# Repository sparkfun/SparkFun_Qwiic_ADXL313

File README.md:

SparkFun 3-Axis Digital Accelerometer Breakout - ADXL313 (Qwiic)
========================================

[*SparkFun 3-Axis Digital Accelerometer Breakout - ADXL313 (Qwiic) (WRL-15663)*](https://www.sparkfun.com/products/17241)

The ADXL313 is a low power, high resolution (up to 13-bits) 3-axis accelerometer for measurement up to ±4g. It measures the static acceleration of gravity in tilt-sensing applications, as well as dynamic acceleration resulting from motion or shock. Digital output data is formatted as 16-bit twos complement and is accessible through the on board Qwiic connectors (I<sup>2</sup>C) or SPI. Its high resolution and low noise enable resolution of inclination changes of as little as 0.1°, while a built-in FIFO facilitates using oversampling techniques to improve resolution to as little as 0.025° of inclination. The integrated 32-level FIFO can also be used to store data to minimize host processor intervention, resulting in reduced system power consumption. Additional low power modes enable intelligent motion-based power management with threshold sensing and active acceleration measurement at extremely low power dissipation. 

Getting the ADXL313 Qwiic breakout set-up is easy. Simply supply the accelerometer with power and communication via the Qwiic connector to your chosen Qwiic development board and you will be good to go. Example use cases for the ADXL313 from Analog Devices include car alarm, hill start aid (HSA) systems, electronic parking brakes, and data recorders applications  (black boxes).

Repository Contents
-------------------

* **/Hardware** - Eagle design files (.brd, .sch)
* **/Hardware/Production** - Production panel files (.brd)

Documentation
--------------
* **[Hookup Guide](https://learn.sparkfun.com/tutorials/sparkfun-qwiic-3-axis-accelerometer-adxl313-hookup-guide)** - Hookup guide for the SparkFun Qwiic 3-Axis Accelerometer (ADXL313)
* **[Product Repository](https://github.com/sparkfun/SparkFun_Qwiic_ADXL313)** - Main hardware repository (including schematic and board design files)

Product Versions
----------------
* [SEN-17241](https://www.sparkfun.com/products/17241)- v1.0, Initial Release

License Information
-------------------

This product is _**open source**_! 

Please review the LICENSE.md file for license information. 

If you have any questions or concerns on licensing, please contact technical support on our [SparkFun forums](https://forum.sparkfun.com/viewforum.php?f=152).

Distributed as-is; no warranty is given.

- Your friends at SparkFun.

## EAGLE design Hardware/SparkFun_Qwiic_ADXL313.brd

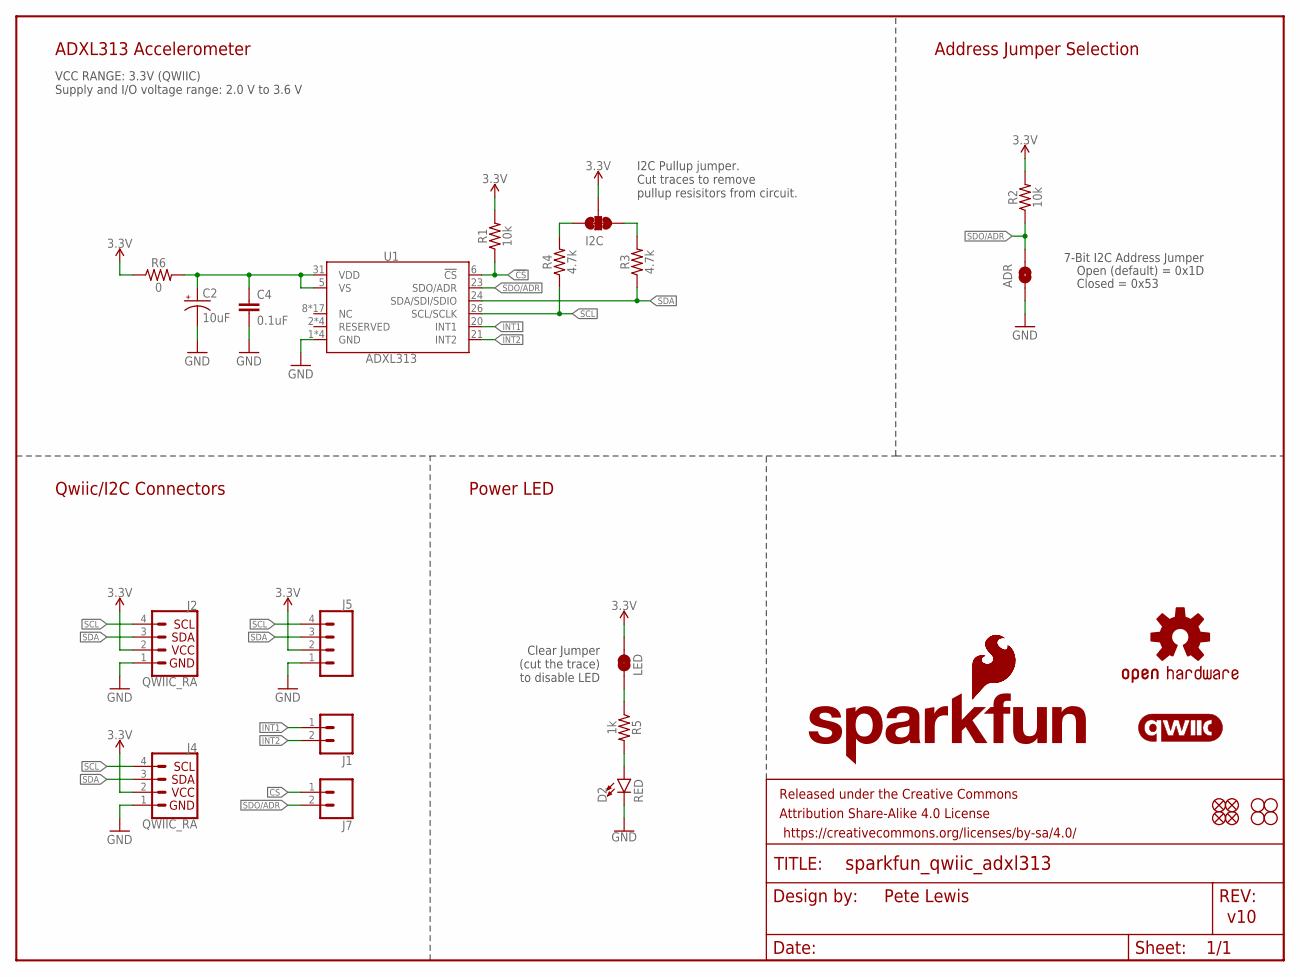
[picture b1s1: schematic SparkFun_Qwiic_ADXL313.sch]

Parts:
ADR: JUMPER-SMT_2_NO_SILK; SMT-JUMPER_2_NO_SILK
C2: 10uF; EIA3216
C4: 0.1uF; 0603
D2: RED; LED-0603
FRAME1: FRAME-LETTER; CREATIVE_COMMONS
I2C: JUMPER-SMT_3_2-NC_TRACE_SILK; SMT-JUMPER_3_2-NC_TRACE_SILK
J1, J7: CONN_021X02_NO_SILK; 1X02_NO_SILK
J2, J4: QWIIC_RA; JST04_1MM_RA
J5: CONN_041X04_NO_SILK; 1X04_NO_SILK
JP1: LED; SMT-JUMPER_2_NC_TRACE_SILK
JP2, JP5, JP6, JP11: FIDUCIALUFIDUCIAL; MICRO-FIDUCIAL
JP3, JP4, JP8, JP9: STAND-OFF
LOGO1: OSHW-LOGOMINI; OSHW-LOGO-MINI
LOGO2: SFE_LOGO_NAME_FLAME.1_INCH; SFE_LOGO_NAME_FLAME_.1
LOGO3: SFE_LOGO_FLAME.1_INCH; SFE_LOGO_FLAME_.1
LOGO4: QWIIC_LOGO_5MM; QWIIC_5MM
R1, R2: 10k; 0603
R3, R4: 4.7k; 0603
R5: 1k; 0603
R6: 0; 0603
U1: ADXL313; LFCSP

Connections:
3.3V: I2C.2, J2.2, J4.2, J5.2, JP1.2, R1.2, R2.2, R6.1
!CS: J7.1, R1.1, U1.6 (!CS)
GND: ADR.1, C2.C (-), C4.2, D2.C, J2.1, J4.1, J5.1, U1.1 (GND), U1.3 (GND), U1.4 (GND), U1.EPAD (GND)
INT1: J1.1, U1.20 (INT1)
INT2: J1.2, U1.21 (INT2)
unnamed: I2C.1, R3.2
unnamed: I2C.3, R4.2
unnamed: C2.A (+), C4.1, R6.2, U1.5 (VS), U1.31 (VDD)
unnamed: D2.A, R5.2
unnamed: JP1.1, R5.1
SCL: J2.4, J4.4, J5.4, R4.1, U1.26 (SCL/SCLK)
SDA: J2.3, J4.3, J5.3, R3.1, U1.24 (SDA/SDI/SDIO)
SDO/ADR: ADR.2, J7.2, R2.1, U1.23 (SDO/ADR)

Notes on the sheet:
7-Bit I2C Address Jumper
Closed = 0x53
Open (default) = 0x1D
Pete Lewis
v10
ADXL313 Accelerometer
Qwiic/I2C Connectors
I2C Pullup jumper. Cut traces to remove pullup resisitors from circuit.
Clear Jumper (cut the trace) to disable LED
Power LED
Address Jumper Selection
VCC RANGE: 3.3V (QWIIC) Supply and I/O voltage range: 2.0 V to 3.6 V

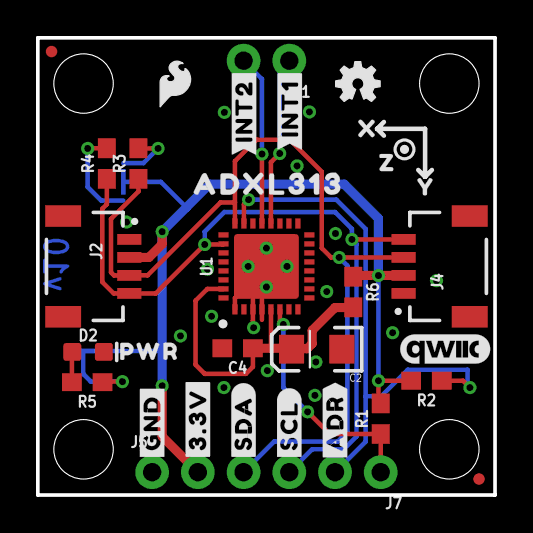
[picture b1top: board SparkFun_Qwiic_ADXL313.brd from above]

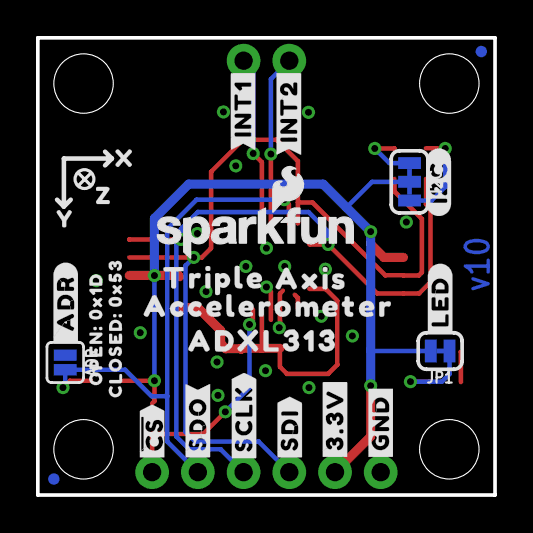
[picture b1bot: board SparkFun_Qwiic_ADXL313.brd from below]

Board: 2 copper layers, 25.4 x 25.4 mm, 63 parts (26 on the bottom side), 13 nets.

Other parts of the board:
U$1: TRIPLE0
U$2: AXIS0
U$3: ACCELEROMETER0
U$4, U$19: ADXL3130
U$5, U$6: #GND#0
U$7, U$8: #3#3V#0
U$9: #SDA#0
U$10: #SDI#0
U$11: #SCL#0
U$12: #_ADR#0
U$13, U$14: #INT2#0
U$15, U$16: #INT1#0
U$17, U$21: X0
U$18: ##CS##0
U$20: #SCLK#0
U$22: OPEN#_0X1D0
U$23: CLOSED#_0X530
U$24: #LED#0
U$25: PWR0
U$26, U$29: Y0
U$27: #I2C#0
U$28: #ADR#0
U$30: #SDO#0
U$31, U$32: Z0

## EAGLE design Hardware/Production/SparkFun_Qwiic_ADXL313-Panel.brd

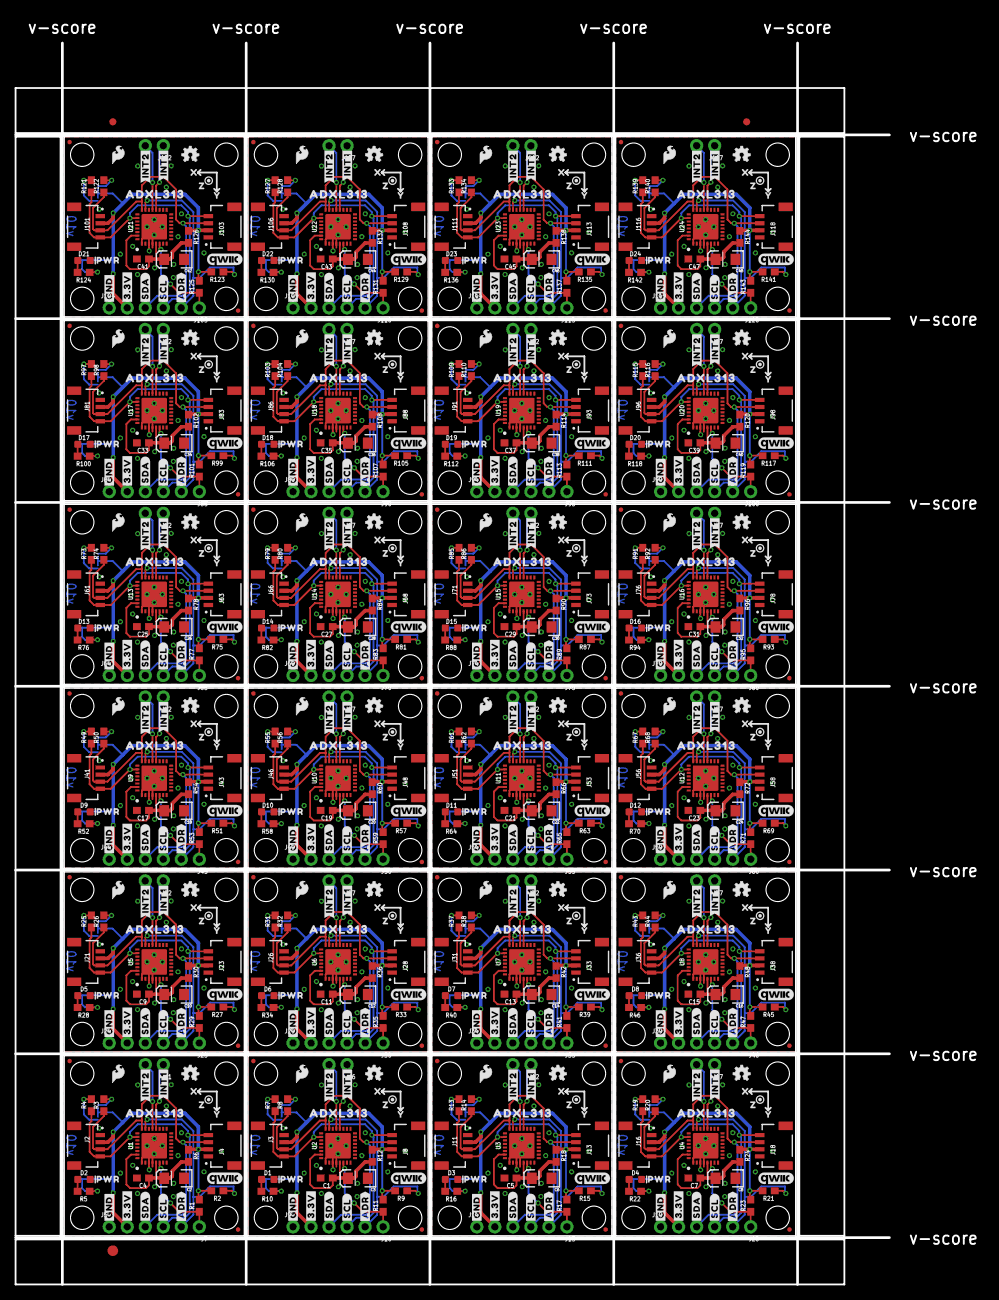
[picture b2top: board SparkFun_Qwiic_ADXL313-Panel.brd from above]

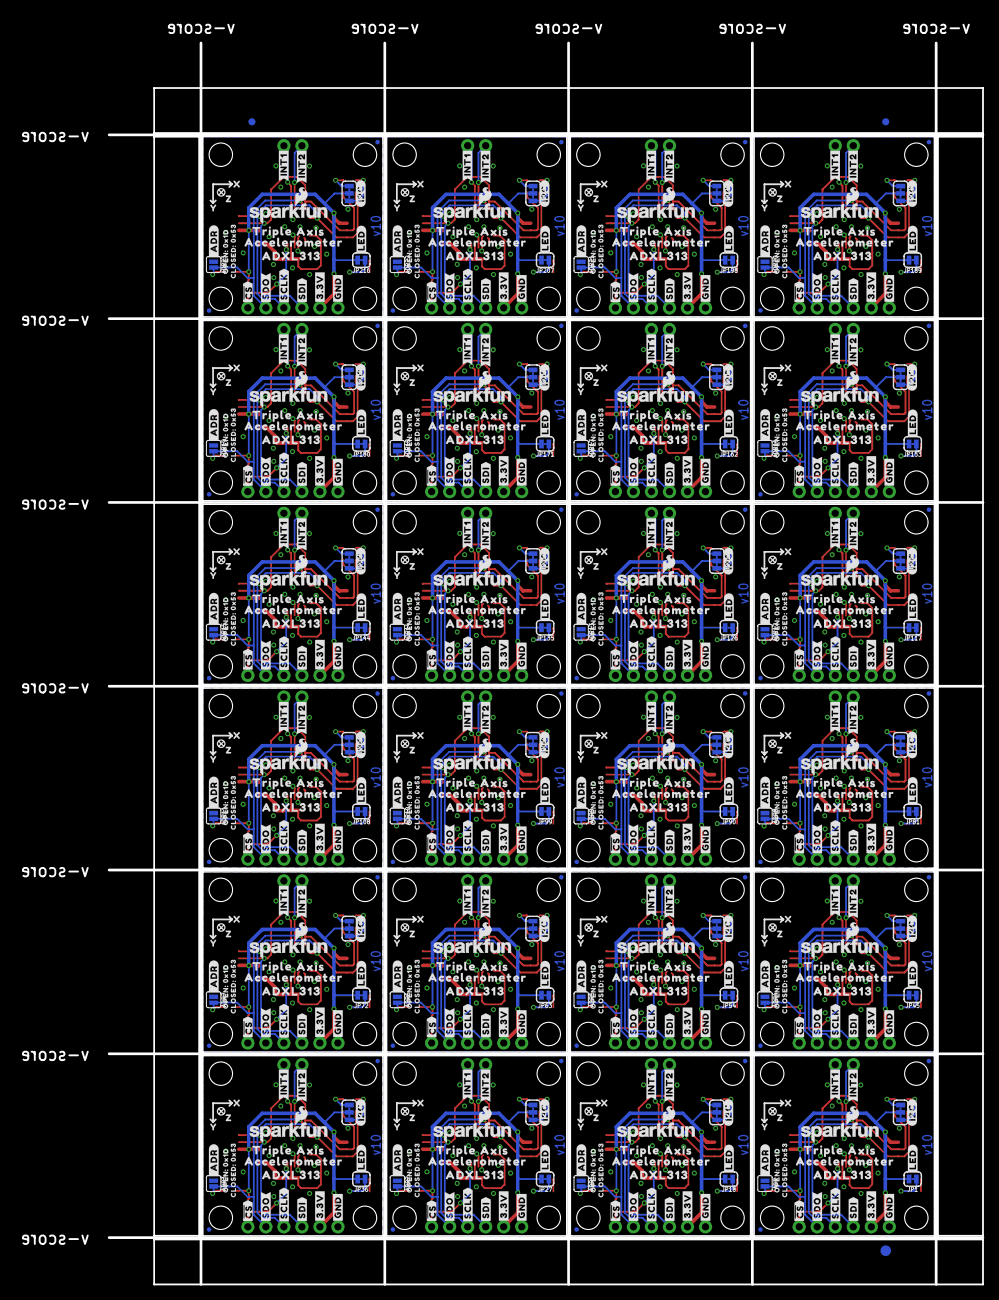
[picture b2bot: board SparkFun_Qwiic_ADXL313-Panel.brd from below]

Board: 2 copper layers, 136.4 x 178.9 mm, 1494 parts (627 on the bottom side), 312 nets.

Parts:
ADR, ADR1, ADR2, ADR3, ADR4, ADR5, ADR6, ADR7, ADR8, ADR9, ADR10, ADR11, ADR12, ADR13, ADR14, ADR15, ADR16, ADR17, ADR18, ADR19, ADR20, ADR21, ADR22, ADR23: SMT-JUMPER_2_NO_SILK
C1, C4, C5, C7, C9, C11, C13, C15, C17, C19, C21, C23, C25, C27, C29, C31, C33, C35, C37, C39, C41, C43, C45, C47: 0.1uF; 0603
C2, C3, C6, C8, C10, C12, C14, C16, C18, C20, C22, C24, C26, C28, C30, C32, C34, C36, C38, C40, C42, C44, C46, C48: 10uF; EIA3216
D1, D2, D3, D4, D5, D6, D7, D8, D9, D10, D11, D12, D13, D14, D15, D16, D17, D18, D19, D20, D21, D22, D23, D24: RED; LED-0603
E$1, E$2, E$3, E$4: FIDUCIAL-1X2
E$5, E$6: FIDUCIAL-1.5X3
I2C, I2C1, I2C2, I2C3, I2C4, I2C5, I2C6, I2C7, I2C8, I2C9, I2C10, I2C11, I2C12, I2C13, I2C14, I2C15, I2C16, I2C17, I2C18, I2C19, I2C20, I2C21, I2C22, I2C23: SMT-JUMPER_3_2-NC_TRACE_SILK
J1, J6, J7, J10, J12, J15, J17, J20, J22, J25, J27, J30, J32, J35, J37, J40, J42, J45, J47, J50, J52, J55, J57, J60, J62, J65, J67, J70, J72, J75, J77, J80, J82, J85, J87, J90, J92, J95, J97, J100, J102, J105, J107, J110, J112, J115, J117, J120: 1X02_NO_SILK
J2, J3, J4, J8, J11, J13, J16, J18, J21, J23, J26, J28, J31, J33, J36, J38, J41, J43, J46, J48, J51, J53, J56, J58, J61, J63, J66, J68, J71, J73, J76, J78, J81, J83, J86, J88, J91, J93, J96, J98, J101, J103, J106, J108, J111, J113, J116, J118: QWIIC_RA; JST04_1MM_RA
J5, J9, J14, J19, J24, J29, J34, J39, J44, J49, J54, J59, J64, J69, J74, J79, J84, J89, J94, J99, J104, J109, J114, J119: 1X04_NO_SILK
JP1, JP18, JP27, JP36, JP45, JP54, JP63, JP72, JP81, JP90, JP99, JP108, JP117, JP126, JP135, JP144, JP153, JP162, JP171, JP180, JP189, JP198, JP207, JP216: LED; SMT-JUMPER_2_NC_TRACE_SILK
JP2, JP5, JP6, JP11, JP12, JP13, JP14, JP15, JP21, JP22, JP23, JP24, JP30, JP31, JP32, JP33, JP39, JP40, JP41, JP42, JP48, JP49, JP50, JP51, JP57, JP58, JP59, JP60, JP66, JP67, JP68, JP69, JP75, JP76, JP77, JP78, JP84, JP85, JP86, JP87, JP93, JP94, JP95, JP96, JP102, JP103, JP104, JP105, JP111, JP112, JP113, JP114, JP120, JP121, JP122, JP123, JP129, JP130, JP131, JP132, JP138, JP139, JP140, JP141, JP147, JP148, JP149, JP150, JP156, JP157, JP158, JP159, JP165, JP166, JP167, JP168, JP174, JP175, JP176, JP177, JP183, JP184, JP185, JP186, JP192, JP193, JP194, JP195, JP201, JP202, JP203, JP204, JP210, JP211, JP212, JP213: FIDUCIALUFIDUCIAL; MICRO-FIDUCIAL
JP3, JP4, JP7, JP8, JP9, JP10, JP16, JP17, JP19, JP20, JP25, JP26, JP28, JP29, JP34, JP35, JP37, JP38, JP43, JP44, JP46, JP47, JP52, JP53, JP55, JP56, JP61, JP62, JP64, JP65, JP70, JP71, JP73, JP74, JP79, JP80, JP82, JP83, JP88, JP89, JP91, JP92, JP97, JP98, JP100, JP101, JP106, JP107, JP109, JP110, JP115, JP116, JP118, JP119, JP124, JP125, JP127, JP128, JP133, JP134, JP136, JP137, JP142, JP143, JP145, JP146, JP151, JP152, JP154, JP155, JP160, JP161, JP163, JP164, JP169, JP170, JP172, JP173, JP178, JP179, JP181, JP182, JP187, JP188, JP190, JP191, JP196, JP197, JP199, JP200, JP205, JP206, JP208, JP209, JP214, JP215: STAND-OFF
LOGO1, LOGO5, LOGO9, LOGO13, LOGO17, LOGO21, LOGO25, LOGO29, LOGO33, LOGO37, LOGO41, LOGO45, LOGO49, LOGO53, LOGO57, LOGO61, LOGO65, LOGO69, LOGO73, LOGO77, LOGO81, LOGO85, LOGO89, LOGO93: OSHW-LOGOMINI; OSHW-LOGO-MINI
LOGO2, LOGO6, LOGO10, LOGO14, LOGO18, LOGO22, LOGO26, LOGO30, LOGO34, LOGO38, LOGO42, LOGO46, LOGO50, LOGO54, LOGO58, LOGO62, LOGO66, LOGO70, LOGO74, LOGO78, LOGO82, LOGO86, LOGO90, LOGO94: SFE_LOGO_NAME_FLAME.1_INCH; SFE_LOGO_NAME_FLAME_.1
LOGO3, LOGO8, LOGO12, LOGO16, LOGO20, LOGO24, LOGO28, LOGO32, LOGO36, LOGO40, LOGO44, LOGO48, LOGO52, LOGO56, LOGO60, LOGO64, LOGO68, LOGO72, LOGO76, LOGO80, LOGO84, LOGO88, LOGO92, LOGO96: SFE_LOGO_FLAME.1_INCH; SFE_LOGO_FLAME_.1
LOGO4, LOGO7, LOGO11, LOGO15, LOGO19, LOGO23, LOGO27, LOGO31, LOGO35, LOGO39, LOGO43, LOGO47, LOGO51, LOGO55, LOGO59, LOGO63, LOGO67, LOGO71, LOGO75, LOGO79, LOGO83, LOGO87, LOGO91, LOGO95: QWIIC_LOGO_5MM; QWIIC_5MM
R1, R2, R9, R11, R15, R17, R21, R23, R27, R29, R33, R35, R39, R41, R45, R47, R51, R53, R57, R59, R63, R65, R69, R71, R75, R77, R81, R83, R87, R89, R93, R95, R99, R101, R105, R107, R111, R113, R117, R119, R123, R125, R129, R131, R135, R137, R141, R143: 10k; 0603
R3, R4, R7, R8, R13, R14, R19, R20, R25, R26, R31, R32, R37, R38, R43, R44, R49, R50, R55, R56, R61, R62, R67, R68, R73, R74, R79, R80, R85, R86, R91, R92, R97, R98, R103, R104, R109, R110, R115, R116, R121, R122, R127, R128, R133, R134, R139, R140: 4.7k; 0603
R5, R10, R16, R22, R28, R34, R40, R46, R52, R58, R64, R70, R76, R82, R88, R94, R100, R106, R112, R118, R124, R130, R136, R142: 1k; 0603
R6, R12, R18, R24, R30, R36, R42, R48, R54, R60, R66, R72, R78, R84, R90, R96, R102, R108, R114, R120, R126, R132, R138, R144: 0; 0603
U1, U2, U3, U4, U5, U6, U7, U8, U9, U10, U11, U12, U13, U14, U15, U16, U17, U18, U19, U20, U21, U22, U23, U24: ADXL313; LFCSP
U$1, U$33, U$65, U$97, U$129, U$161, U$193, U$225, U$257, U$289, U$321, U$353, U$385, U$417, U$449, U$481, U$513, U$545, U$577, U$609, U$641, U$673, U$705, U$737: TRIPLE0
U$2, U$34, U$66, U$98, U$130, U$162, U$194, U$226, U$258, U$290, U$322, U$354, U$386, U$418, U$450, U$482, U$514, U$546, U$578, U$610, U$642, U$674, U$706, U$738: AXIS0
U$3, U$35, U$67, U$99, U$131, U$163, U$195, U$227, U$259, U$291, U$323, U$355, U$387, U$419, U$451, U$483, U$515, U$547, U$579, U$611, U$643, U$675, U$707, U$739: ACCELEROMETER0
U$4, U$19, U$36, U$52, U$68, U$84, U$100, U$116, U$132, U$148, U$164, U$180, U$196, U$212, U$228, U$244, U$260, U$276, U$292, U$308, U$324, U$340, U$356, U$372, U$388, U$404, U$420, U$436, U$452, U$468, U$484, U$500, U$516, U$532, U$548, U$564, U$580, U$596, U$612, U$628, U$644, U$660, U$676, U$692, U$708, U$724, U$740, U$756: ADXL3130
U$5, U$6, U$37, U$38, U$69, U$70, U$101, U$102, U$133, U$134, U$165, U$166, U$197, U$198, U$229, U$230, U$261, U$262, U$293, U$294, U$325, U$326, U$357, U$358, U$389, U$390, U$421, U$422, U$453, U$454, U$485, U$486, U$517, U$518, U$549, U$550, U$581, U$582, U$613, U$614, U$645, U$646, U$677, U$678, U$709, U$710, U$741, U$742: #GND#0
U$7, U$8, U$39, U$40, U$71, U$72, U$103, U$104, U$135, U$136, U$167, U$168, U$199, U$200, U$231, U$232, U$263, U$264, U$295, U$296, U$327, U$328, U$359, U$360, U$391, U$392, U$423, U$424, U$455, U$456, U$487, U$488, U$519, U$520, U$551, U$552, U$583, U$584, U$615, U$616, U$647, U$648, U$679, U$680, U$711, U$712, U$743, U$744: #3#3V#0
U$9, U$41, U$73, U$105, U$137, U$169, U$201, U$233, U$265, U$297, U$329, U$361, U$393, U$425, U$457, U$489, U$521, U$553, U$585, U$617, U$649, U$681, U$713, U$745: #SDA#0
U$10, U$56, U$88, U$120, U$152, U$184, U$216, U$248, U$280, U$312, U$344, U$376, U$408, U$440, U$472, U$504, U$536, U$568, U$600, U$632, U$664, U$696, U$728, U$760: #SDI#0
U$11, U$42, U$74, U$106, U$138, U$170, U$202, U$234, U$266, U$298, U$330, U$362, U$394, U$426, U$458, U$490, U$522, U$554, U$586, U$618, U$650, U$682, U$714, U$746: #SCL#0
U$12, U$58, U$90, U$122, U$154, U$186, U$218, U$250, U$282, U$314, U$346, U$378, U$410, U$442, U$474, U$506, U$538, U$570, U$602, U$634, U$666, U$698, U$730, U$762: #_ADR#0
U$13, U$14, U$43, U$44, U$75, U$76, U$107, U$108, U$139, U$140, U$171, U$172, U$203, U$204, U$235, U$236, U$267, U$268, U$299, U$300, U$331, U$332, U$363, U$364, U$395, U$396, U$427, U$428, U$459, U$460, U$491, U$492, U$523, U$524, U$555, U$556, U$587, U$588, U$619, U$620, U$651, U$652, U$683, U$684, U$715, U$716, U$747, U$748: #INT2#0
U$15, U$16, U$45, U$46, U$77, U$78, U$109, U$110, U$141, U$142, U$173, U$174, U$205, U$206, U$237, U$238, U$269, U$270, U$301, U$302, U$333, U$334, U$365, U$366, U$397, U$398, U$429, U$430, U$461, U$462, U$493, U$494, U$525, U$526, U$557, U$558, U$589, U$590, U$621, U$622, U$653, U$654, U$685, U$686, U$717, U$718, U$749, U$750: #INT1#0
U$17, U$21, U$59, U$60, U$91, U$92, U$123, U$124, U$155, U$156, U$187, U$188, U$219, U$220, U$251, U$252, U$283, U$284, U$315, U$316, U$347, U$348, U$379, U$380, U$411, U$412, U$443, U$444, U$475, U$476, U$507, U$508, U$539, U$540, U$571, U$572, U$603, U$604, U$635, U$636, U$667, U$668, U$699, U$700, U$731, U$732, U$763, U$764: X0
U$18, U$47, U$79, U$111, U$143, U$175, U$207, U$239, U$271, U$303, U$335, U$367, U$399, U$431, U$463, U$495, U$527, U$559, U$591, U$623, U$655, U$687, U$719, U$751: ##CS##0
U$20, U$57, U$89, U$121, U$153, U$185, U$217, U$249, U$281, U$313, U$345, U$377, U$409, U$441, U$473, U$505, U$537, U$569, U$601, U$633, U$665, U$697, U$729, U$761: #SCLK#0
U$22, U$48, U$80, U$112, U$144, U$176, U$208, U$240, U$272, U$304, U$336, U$368, U$400, U$432, U$464, U$496, U$528, U$560, U$592, U$624, U$656, U$688, U$720, U$752: OPEN#_0X1D0
U$23, U$49, U$81, U$113, U$145, U$177, U$209, U$241, U$273, U$305, U$337, U$369, U$401, U$433, U$465, U$497, U$529, U$561, U$593, U$625, U$657, U$689, U$721, U$753: CLOSED#_0X530
U$24, U$50, U$82, U$114, U$146, U$178, U$210, U$242, U$274, U$306, U$338, U$370, U$402, U$434, U$466, U$498, U$530, U$562, U$594, U$626, U$658, U$690, U$722, U$754: #LED#0
U$25, U$51, U$83, U$115, U$147, U$179, U$211, U$243, U$275, U$307, U$339, U$371, U$403, U$435, U$467, U$499, U$531, U$563, U$595, U$627, U$659, U$691, U$723, U$755: PWR0
U$26, U$29, U$61, U$62, U$93, U$94, U$125, U$126, U$157, U$158, U$189, U$190, U$221, U$222, U$253, U$254, U$285, U$286, U$317, U$318, U$349, U$350, U$381, U$382, U$413, U$414, U$445, U$446, U$477, U$478, U$509, U$510, U$541, U$542, U$573, U$574, U$605, U$606, U$637, U$638, U$669, U$670, U$701, U$702, U$733, U$734, U$765, U$766: Y0
U$27, U$53, U$85, U$117, U$149, U$181, U$213, U$245, U$277, U$309, U$341, U$373, U$405, U$437, U$469, U$501, U$533, U$565, U$597, U$629, U$661, U$693, U$725, U$757: #I2C#0
U$28, U$55, U$87, U$119, U$151, U$183, U$215, U$247, U$279, U$311, U$343, U$375, U$407, U$439, U$471, U$503, U$535, U$567, U$599, U$631, U$663, U$695, U$727, U$759: #ADR#0
U$30, U$54, U$86, U$118, U$150, U$182, U$214, U$246, U$278, U$310, U$342, U$374, U$406, U$438, U$470, U$502, U$534, U$566, U$598, U$630, U$662, U$694, U$726, U$758: #SDO#0
U$31, U$32, U$63, U$64, U$95, U$96, U$127, U$128, U$159, U$160, U$191, U$192, U$223, U$224, U$255, U$256, U$287, U$288, U$319, U$320, U$351, U$352, U$383, U$384, U$415, U$416, U$447, U$448, U$479, U$480, U$511, U$512, U$543, U$544, U$575, U$576, U$607, U$608, U$639, U$640, U$671, U$672, U$703, U$704, U$735, U$736, U$767, U$768: Z0

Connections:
3.3V: I2C.2, J2.2, J4.2, J5.2, JP1.2, R1.2, R2.2, R6.1
3.3V1: I2C1.2, J3.2, J8.2, J9.2, JP18.2, R9.2, R11.2, R12.1
3.3V2: I2C2.2, J11.2, J13.2, J14.2, JP27.2, R15.2, R17.2, R18.1
3.3V3: I2C3.2, J16.2, J18.2, J19.2, JP36.2, R21.2, R23.2, R24.1
3.3V4: I2C4.2, J21.2, J23.2, J24.2, JP45.2, R27.2, R29.2, R30.1
3.3V5: I2C5.2, J26.2, J28.2, J29.2, JP54.2, R33.2, R35.2, R36.1
3.3V6: I2C6.2, J31.2, J33.2, J34.2, JP63.2, R39.2, R41.2, R42.1
3.3V7: I2C7.2, J36.2, J38.2, J39.2, JP72.2, R45.2, R47.2, R48.1
3.3V8: I2C8.2, J41.2, J43.2, J44.2, JP81.2, R51.2, R53.2, R54.1
3.3V9: I2C9.2, J46.2, J48.2, J49.2, JP90.2, R57.2, R59.2, R60.1
3.3V10: I2C10.2, J51.2, J53.2, J54.2, JP99.2, R63.2, R65.2, R66.1
3.3V11: I2C11.2, J56.2, J58.2, J59.2, JP108.2, R69.2, R71.2, R72.1
3.3V12: I2C12.2, J61.2, J63.2, J64.2, JP117.2, R75.2, R77.2, R78.1
3.3V13: I2C13.2, J66.2, J68.2, J69.2, JP126.2, R81.2, R83.2, R84.1
3.3V14: I2C14.2, J71.2, J73.2, J74.2, JP135.2, R87.2, R89.2, R90.1
3.3V15: I2C15.2, J76.2, J78.2, J79.2, JP144.2, R93.2, R95.2, R96.1
3.3V16: I2C16.2, J81.2, J83.2, J84.2, JP153.2, R99.2, R101.2, R102.1
3.3V17: I2C17.2, J86.2, J88.2, J89.2, JP162.2, R105.2, R107.2, R108.1
3.3V18: I2C18.2, J91.2, J93.2, J94.2, JP171.2, R111.2, R113.2, R114.1
3.3V19: I2C19.2, J96.2, J98.2, J99.2, JP180.2, R117.2, R119.2, R120.1
3.3V20: I2C20.2, J101.2, J103.2, J104.2, JP189.2, R123.2, R125.2, R126.1
3.3V21: I2C21.2, J106.2, J108.2, J109.2, JP198.2, R129.2, R131.2, R132.1
3.3V22: I2C22.2, J111.2, J113.2, J114.2, JP207.2, R135.2, R137.2, R138.1
3.3V23: I2C23.2, J116.2, J118.2, J119.2, JP216.2, R141.2, R143.2, R144.1
!CS: J7.1, R1.1, U1.6
!CS1: J10.1, R11.1, U2.6
!CS2: J15.1, R17.1, U3.6
!CS3: J20.1, R23.1, U4.6
!CS4: J25.1, R29.1, U5.6
!CS5: J30.1, R35.1, U6.6
!CS6: J35.1, R41.1, U7.6
!CS7: J40.1, R47.1, U8.6
!CS8: J45.1, R53.1, U9.6
!CS9: J50.1, R59.1, U10.6
!CS10: J55.1, R65.1, U11.6
!CS11: J60.1, R71.1, U12.6
!CS12: J65.1, R77.1, U13.6
!CS13: J70.1, R83.1, U14.6
!CS14: J75.1, R89.1, U15.6
!CS15: J80.1, R95.1, U16.6
!CS16: J85.1, R101.1, U17.6
!CS17: J90.1, R107.1, U18.6
!CS18: J95.1, R113.1, U19.6
!CS19: J100.1, R119.1, U20.6
!CS20: J105.1, R125.1, U21.6
!CS21: J110.1, R131.1, U22.6
!CS22: J115.1, R137.1, U23.6
!CS23: J120.1, R143.1, U24.6
GND: ADR.1, C2.C, C4.2, D2.C, J2.1, J4.1, J5.1, U1.1, U1.3, U1.4, U1.EPAD
GND1: ADR1.1, C1.2, C3.C, D1.C, J3.1, J8.1, J9.1, U2.1, U2.3, U2.4, U2.EPAD
GND2: ADR2.1, C5.2, C6.C, D3.C, J11.1, J13.1, J14.1, U3.1, U3.3, U3.4, U3.EPAD
GND3: ADR3.1, C7.2, C8.C, D4.C, J16.1, J18.1, J19.1, U4.1, U4.3, U4.4, U4.EPAD
GND4: ADR4.1, C9.2, C10.C, D5.C, J21.1, J23.1, J24.1, U5.1, U5.3, U5.4, U5.EPAD
GND5: ADR5.1, C11.2, C12.C, D6.C, J26.1, J28.1, J29.1, U6.1, U6.3, U6.4, U6.EPAD
GND6: ADR6.1, C13.2, C14.C, D7.C, J31.1, J33.1, J34.1, U7.1, U7.3, U7.4, U7.EPAD
GND7: ADR7.1, C15.2, C16.C, D8.C, J36.1, J38.1, J39.1, U8.1, U8.3, U8.4, U8.EPAD
GND8: ADR8.1, C17.2, C18.C, D9.C, J41.1, J43.1, J44.1, U9.1, U9.3, U9.4, U9.EPAD
GND9: ADR9.1, C19.2, C20.C, D10.C, J46.1, J48.1, J49.1, U10.1, U10.3, U10.4, U10.EPAD
GND10: ADR10.1, C21.2, C22.C, D11.C, J51.1, J53.1, J54.1, U11.1, U11.3, U11.4, U11.EPAD
GND11: ADR11.1, C23.2, C24.C, D12.C, J56.1, J58.1, J59.1, U12.1, U12.3, U12.4, U12.EPAD
GND12: ADR12.1, C25.2, C26.C, D13.C, J61.1, J63.1, J64.1, U13.1, U13.3, U13.4, U13.EPAD
GND13: ADR13.1, C27.2, C28.C, D14.C, J66.1, J68.1, J69.1, U14.1, U14.3, U14.4, U14.EPAD
GND14: ADR14.1, C29.2, C30.C, D15.C, J71.1, J73.1, J74.1, U15.1, U15.3, U15.4, U15.EPAD
GND15: ADR15.1, C31.2, C32.C, D16.C, J76.1, J78.1, J79.1, U16.1, U16.3, U16.4, U16.EPAD
GND16: ADR16.1, C33.2, C34.C, D17.C, J81.1, J83.1, J84.1, U17.1, U17.3, U17.4, U17.EPAD
GND17: ADR17.1, C35.2, C36.C, D18.C, J86.1, J88.1, J89.1, U18.1, U18.3, U18.4, U18.EPAD
GND18: ADR18.1, C37.2, C38.C, D19.C, J91.1, J93.1, J94.1, U19.1, U19.3, U19.4, U19.EPAD
GND19: ADR19.1, C39.2, C40.C, D20.C, J96.1, J98.1, J99.1, U20.1, U20.3, U20.4, U20.EPAD
GND20: ADR20.1, C41.2, C42.C, D21.C, J101.1, J103.1, J104.1, U21.1, U21.3, U21.4, U21.EPAD
GND21: ADR21.1, C43.2, C44.C, D22.C, J106.1, J108.1, J109.1, U22.1, U22.3, U22.4, U22.EPAD
GND22: ADR22.1, C45.2, C46.C, D23.C, J111.1, J113.1, J114.1, U23.1, U23.3, U23.4, U23.EPAD
GND23: ADR23.1, C47.2, C48.C, D24.C, J116.1, J118.1, J119.1, U24.1, U24.3, U24.4, U24.EPAD
INT1: J1.1, U1.20
INT2: J1.2, U1.21
INT3: J6.2, U2.21
INT4: J6.1, U2.20
INT5: J12.2, U3.21
INT6: J12.1, U3.20
INT7: J17.2, U4.21
INT8: J17.1, U4.20
INT9: J22.2, U5.21
INT10: J22.1, U5.20
INT11: J27.2, U6.21
INT12: J27.1, U6.20
INT13: J32.2, U7.21
INT14: J32.1, U7.20
INT15: J37.2, U8.21
INT16: J37.1, U8.20
INT17: J42.2, U9.21
INT18: J42.1, U9.20
INT19: J47.2, U10.21
INT20: J47.1, U10.20
INT21: J52.2, U11.21
INT22: J52.1, U11.20
INT23: J57.2, U12.21
INT24: J57.1, U12.20
INT25: J62.2, U13.21
INT26: J62.1, U13.20
INT27: J67.2, U14.21
INT28: J67.1, U14.20
INT29: J72.2, U15.21
INT30: J72.1, U15.20
INT31: J77.2, U16.21
INT32: J77.1, U16.20
INT33: J82.2, U17.21
INT34: J82.1, U17.20
INT35: J87.2, U18.21
INT36: J87.1, U18.20
INT37: J92.2, U19.21
INT38: J92.1, U19.20
INT39: J97.2, U20.21
INT40: J97.1, U20.20
INT41: J102.2, U21.21
INT42: J102.1, U21.20
INT43: J107.2, U22.21
INT44: J107.1, U22.20
INT45: J112.2, U23.21
INT46: J112.1, U23.20
INT47: J117.2, U24.21
INT48: J117.1, U24.20
unnamed: I2C.1, R3.2
unnamed: I2C.3, R4.2
unnamed: C2.A, C4.1, R6.2, U1.5, U1.31
unnamed: I2C1.1, R8.2
unnamed: I2C1.3, R7.2
unnamed: D2.A, R5.2
unnamed: D1.A, R10.2
unnamed: JP1.1, R5.1
unnamed: JP18.1, R10.1
unnamed: C1.1, C3.A, R12.2, U2.5, U2.31
unnamed: I2C2.1, R14.2
unnamed: I2C2.3, R13.2
unnamed: D3.A, R16.2
unnamed: JP27.1, R16.1
unnamed: C5.1, C6.A, R18.2, U3.5, U3.31
unnamed: I2C3.1, R20.2
unnamed: I2C3.3, R19.2
unnamed: D4.A, R22.2
unnamed: JP36.1, R22.1
unnamed: C7.1, C8.A, R24.2, U4.5, U4.31
unnamed: I2C4.1, R26.2
unnamed: I2C4.3, R25.2
unnamed: D5.A, R28.2
unnamed: JP45.1, R28.1
unnamed: C9.1, C10.A, R30.2, U5.5, U5.31
unnamed: I2C5.1, R32.2
unnamed: I2C5.3, R31.2
unnamed: D6.A, R34.2
unnamed: JP54.1, R34.1
unnamed: C11.1, C12.A, R36.2, U6.5, U6.31
unnamed: I2C6.1, R38.2
unnamed: I2C6.3, R37.2
unnamed: D7.A, R40.2
unnamed: JP63.1, R40.1
unnamed: C13.1, C14.A, R42.2, U7.5, U7.31
unnamed: I2C7.1, R44.2
unnamed: I2C7.3, R43.2
unnamed: D8.A, R46.2
unnamed: JP72.1, R46.1
unnamed: C15.1, C16.A, R48.2, U8.5, U8.31
unnamed: I2C8.1, R50.2
unnamed: I2C8.3, R49.2
unnamed: D9.A, R52.2
unnamed: JP81.1, R52.1
unnamed: C17.1, C18.A, R54.2, U9.5, U9.31
unnamed: I2C9.1, R56.2
unnamed: I2C9.3, R55.2
unnamed: D10.A, R58.2
unnamed: JP90.1, R58.1
unnamed: C19.1, C20.A, R60.2, U10.5, U10.31
unnamed: I2C10.1, R62.2
unnamed: I2C10.3, R61.2
unnamed: D11.A, R64.2
unnamed: JP99.1, R64.1
unnamed: C21.1, C22.A, R66.2, U11.5, U11.31
unnamed: I2C11.1, R68.2
unnamed: I2C11.3, R67.2
unnamed: D12.A, R70.2
unnamed: JP108.1, R70.1
unnamed: C23.1, C24.A, R72.2, U12.5, U12.31
unnamed: I2C12.1, R74.2
unnamed: I2C12.3, R73.2
unnamed: D13.A, R76.2
unnamed: JP117.1, R76.1
unnamed: C25.1, C26.A, R78.2, U13.5, U13.31
unnamed: I2C13.1, R80.2
unnamed: I2C13.3, R79.2
unnamed: D14.A, R82.2
unnamed: JP126.1, R82.1
unnamed: C27.1, C28.A, R84.2, U14.5, U14.31
unnamed: I2C14.1, R86.2
unnamed: I2C14.3, R85.2
unnamed: D15.A, R88.2
unnamed: JP135.1, R88.1
unnamed: C29.1, C30.A, R90.2, U15.5, U15.31
unnamed: I2C15.1, R92.2
unnamed: I2C15.3, R91.2
unnamed: D16.A, R94.2
unnamed: JP144.1, R94.1
unnamed: C31.1, C32.A, R96.2, U16.5, U16.31
unnamed: I2C16.1, R98.2
unnamed: I2C16.3, R97.2
unnamed: D17.A, R100.2
unnamed: JP153.1, R100.1
unnamed: C33.1, C34.A, R102.2, U17.5, U17.31
unnamed: I2C17.1, R104.2
unnamed: I2C17.3, R103.2
unnamed: D18.A, R106.2
unnamed: JP162.1, R106.1
unnamed: C35.1, C36.A, R108.2, U18.5, U18.31
unnamed: I2C18.1, R110.2
unnamed: I2C18.3, R109.2
unnamed: D19.A, R112.2
unnamed: JP171.1, R112.1
unnamed: C37.1, C38.A, R114.2, U19.5, U19.31
unnamed: I2C19.1, R116.2
unnamed: I2C19.3, R115.2
unnamed: D20.A, R118.2
unnamed: JP180.1, R118.1
unnamed: C39.1, C40.A, R120.2, U20.5, U20.31
unnamed: I2C20.1, R122.2
unnamed: I2C20.3, R121.2
unnamed: D21.A, R124.2
unnamed: JP189.1, R124.1
unnamed: C41.1, C42.A, R126.2, U21.5, U21.31
unnamed: I2C21.1, R128.2
unnamed: I2C21.3, R127.2
unnamed: D22.A, R130.2
unnamed: JP198.1, R130.1
unnamed: C43.1, C44.A, R132.2, U22.5, U22.31
unnamed: I2C22.1, R134.2
unnamed: I2C22.3, R133.2
unnamed: D23.A, R136.2
unnamed: JP207.1, R136.1
unnamed: C45.1, C46.A, R138.2, U23.5, U23.31
unnamed: I2C23.1, R140.2
unnamed: I2C23.3, R139.2
unnamed: D24.A, R142.2
unnamed: JP216.1, R142.1
unnamed: C47.1, C48.A, R144.2, U24.5, U24.31
SCL: J2.4, J4.4, J5.4, R4.1, U1.26
SCL1: J3.4, J8.4, J9.4, R7.1, U2.26
SCL2: J11.4, J13.4, J14.4, R13.1, U3.26
SCL3: J16.4, J18.4, J19.4, R19.1, U4.26
SCL4: J21.4, J23.4, J24.4, R25.1, U5.26
SCL5: J26.4, J28.4, J29.4, R31.1, U6.26
SCL6: J31.4, J33.4, J34.4, R37.1, U7.26
SCL7: J36.4, J38.4, J39.4, R43.1, U8.26
SCL8: J41.4, J43.4, J44.4, R49.1, U9.26
SCL9: J46.4, J48.4, J49.4, R55.1, U10.26
SCL10: J51.4, J53.4, J54.4, R61.1, U11.26
SCL11: J56.4, J58.4, J59.4, R67.1, U12.26
SCL12: J61.4, J63.4, J64.4, R73.1, U13.26
SCL13: J66.4, J68.4, J69.4, R79.1, U14.26
SCL14: J71.4, J73.4, J74.4, R85.1, U15.26
SCL15: J76.4, J78.4, J79.4, R91.1, U16.26
SCL16: J81.4, J83.4, J84.4, R97.1, U17.26
SCL17: J86.4, J88.4, J89.4, R103.1, U18.26
SCL18: J91.4, J93.4, J94.4, R109.1, U19.26
SCL19: J96.4, J98.4, J99.4, R115.1, U20.26
SCL20: J101.4, J103.4, J104.4, R121.1, U21.26
SCL21: J106.4, J108.4, J109.4, R127.1, U22.26
SCL22: J111.4, J113.4, J114.4, R133.1, U23.26
SCL23: J116.4, J118.4, J119.4, R139.1, U24.26
SDA: J2.3, J4.3, J5.3, R3.1, U1.24
SDA1: J3.3, J8.3, J9.3, R8.1, U2.24
SDA2: J11.3, J13.3, J14.3, R14.1, U3.24
SDA3: J16.3, J18.3, J19.3, R20.1, U4.24
SDA4: J21.3, J23.3, J24.3, R26.1, U5.24
SDA5: J26.3, J28.3, J29.3, R32.1, U6.24
SDA6: J31.3, J33.3, J34.3, R38.1, U7.24
SDA7: J36.3, J38.3, J39.3, R44.1, U8.24
SDA8: J41.3, J43.3, J44.3, R50.1, U9.24
SDA9: J46.3, J48.3, J49.3, R56.1, U10.24
SDA10: J51.3, J53.3, J54.3, R62.1, U11.24
SDA11: J56.3, J58.3, J59.3, R68.1, U12.24
SDA12: J61.3, J63.3, J64.3, R74.1, U13.24
SDA13: J66.3, J68.3, J69.3, R80.1, U14.24
SDA14: J71.3, J73.3, J74.3, R86.1, U15.24
SDA15: J76.3, J78.3, J79.3, R92.1, U16.24
SDA16: J81.3, J83.3, J84.3, R98.1, U17.24
SDA17: J86.3, J88.3, J89.3, R104.1, U18.24
SDA18: J91.3, J93.3, J94.3, R110.1, U19.24
SDA19: J96.3, J98.3, J99.3, R116.1, U20.24
SDA20: J101.3, J103.3, J104.3, R122.1, U21.24
SDA21: J106.3, J108.3, J109.3, R128.1, U22.24
SDA22: J111.3, J113.3, J114.3, R134.1, U23.24
SDA23: J116.3, J118.3, J119.3, R140.1, U24.24
SDO/ADR: ADR.2, J7.2, R2.1, U1.23
SDO/ADR1: ADR1.2, J10.2, R9.1, U2.23
SDO/ADR2: ADR2.2, J15.2, R15.1, U3.23
SDO/ADR3: ADR3.2, J20.2, R21.1, U4.23
SDO/ADR4: ADR4.2, J25.2, R27.1, U5.23
SDO/ADR5: ADR5.2, J30.2, R33.1, U6.23
SDO/ADR6: ADR6.2, J35.2, R39.1, U7.23
SDO/ADR7: ADR7.2, J40.2, R45.1, U8.23
SDO/ADR8: ADR8.2, J45.2, R51.1, U9.23
SDO/ADR9: ADR9.2, J50.2, R57.1, U10.23
SDO/ADR10: ADR10.2, J55.2, R63.1, U11.23
SDO/ADR11: ADR11.2, J60.2, R69.1, U12.23
SDO/ADR12: ADR12.2, J65.2, R75.1, U13.23
SDO/ADR13: ADR13.2, J70.2, R81.1, U14.23
SDO/ADR14: ADR14.2, J75.2, R87.1, U15.23
SDO/ADR15: ADR15.2, J80.2, R93.1, U16.23
SDO/ADR16: ADR16.2, J85.2, R99.1, U17.23
SDO/ADR17: ADR17.2, J90.2, R105.1, U18.23
SDO/ADR18: ADR18.2, J95.2, R111.1, U19.23
SDO/ADR19: ADR19.2, J100.2, R117.1, U20.23
SDO/ADR20: ADR20.2, J105.2, R123.1, U21.23
SDO/ADR21: ADR21.2, J110.2, R129.1, U22.23
SDO/ADR22: ADR22.2, J115.2, R135.1, U23.23
SDO/ADR23: ADR23.2, J120.2, R141.1, U24.23

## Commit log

2020-09-14 v01 sch import done. ready for layout
2020-09-14 pullup on CS for default I2C mode (aka mode jumper)
2020-09-14 routing done
2020-09-15 ENG checklist run changes - pre-group review
    -sch cleanup
    -PROD_ID for IC
    -GND stiching vias and re-routed 3.3V near IC for better GND return path from filter caps
    -approve DRC errors (jumper overlaps and some stubs)
    -more measures
2020-09-17 Group Review changes
    -Removed MODE Jumper, CS should always be tied high.
    -Added optional Resistor on power input to IC, for potential RC filter.
    -SDA/SCL corrected
    - corrected pin location in device footprint. (they were mirrored)
    - 3 vias under IC are now actually named GND
    - CS and SDO were swapped with INTs so all data lines are on the same row of headers
2020-09-18 More changes from review #2
    -INPUTS and OUTPUT silk flags corrected
    -XYZ axis silk rotated 90 degress to match IC axis. on both top and bottom silk.
    -Removed label on top silk for CS pin (because it's not part of I2C).
    -Swapped CD and ADR/SDO, so that all I2C pins are in a a row.
    -Changed ADR silk label on top so that it is an INPUT flag silk type
    -rotated I2C jumper (and silk) so that all bottom silk reads the same direction.
2020-09-18 DRC error approval
2020-09-21 Axis label correction
    -also updated xyz letters to buzzard text labels
2020-09-21 ran checklist - moved one via to avoid silk label
2020-10-28 production panel files
2020-11-04 replaced ADXL313 with device in main eagle Sensor library

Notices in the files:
parts and their libraries:
SparkFun-Resistors: Licensing: Creative Commons ShareAlike 4.0 International - https://creativecommons.org/licenses/by-sa/4.0
SparkFun-Aesthetics: Released under the Creative Commons Attribution Share-Alike 4.0 License
SparkFun-Aesthetics: https://creativecommons.org/licenses/by-sa/4.0
